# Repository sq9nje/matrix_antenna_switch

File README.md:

# 6x2 Matrix Antenna Switch

A complete antenna switching system that allows connecting two transceivers to up to 6 antennas with intelligent control and protection.

## Overview

This project implements a 6x2 matrix antenna switch system consisting of two main modules:

- **Relay Module**: High-power RF switching matrix with electromechanical relays
- **Interface Module**: ESP32-based control system with RS485 communication

The system provides flexible antenna routing while preventing simultaneous connection of both transceivers to the same antenna, ensuring equipment protection and operational safety.

## Key Features

### RF Performance
- **Power Handling**: Up to 1.5kW (full amateur license power)
- **Frequency Range**: DC to 50+ MHz with good performance
- **Protection**: Gas discharge tubes on all antenna ports for lightning/ESD protection
- **Isolation**: Decent port-to-port isolation
  - Better than 75dB below 10MHz
  - Better than 65dB below 30MHz
  - Better than 50dB below 50MHz

### Control System
- **ESP32-based**: WiFi-enabled microcontroller with comprehensive firmware
- **Multiple Interfaces**: Web UI, REST API, WebSocket, and serial command control
- **Network Features**: mDNS discovery (`antenna.local`), OTA updates, WiFi management
- **Smart Features**: Antenna conflict prevention, single radio mode, persistent settings
- **RS485 Interface**: Reliable half-duplex communication with automatic direction detection
- **Expandability**: SAO (Simple Add-On) connector for future enhancements

### Design Features
- **Modular Architecture**: Separate relay and interface modules for flexibility
- **Three-Relay Configuration**: Prevents transceiver conflicts while maintaining isolation
- **Professional PCB Design**: Multi-layer boards with proper grounding and shielding
- **Easy Assembly**: Through-hole components for straightforward construction

## System Architecture

The complete system consists of:

1. **[Relay Module](relay_module/hardware/README.md)**:
   - 6 antenna sections, each with 3 relays
   - Allows connection to Radio 1, Radio 2, or 50Ω dummy load
   - Comprehensive protection circuitry

2. **[Interface Module](interface_module/hardware/README.md)**: Provides intelligent control and communication
   - ESP32 DevKit v1 for processing and connectivity
   - RS485 interface for remote control
   - Expansion connector for additional features

## Documentation

### Hardware Documentation
- **[Relay Module Hardware](relay_module/hardware/README.md)** - Complete RF switching matrix documentation
- **[Interface Module Hardware](interface_module/hardware/README.md)** - ESP32 control system hardware

### Firmware Documentation  
- **[Interface Module Firmware](interface_module/firmware/README.md)** - ESP32 firmware with web interface, REST API, and OTA updates

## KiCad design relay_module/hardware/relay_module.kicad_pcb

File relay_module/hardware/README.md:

# Relay Module Hardware

This directory contains all hardware design files for the 6x2 Matrix Antenna Switch relay module, designed in KiCad.

## Overview

The relay module is a part of a 6x2 matrix antenna switch. It consists of six identical sections, one for each antenna. Each section allows connecting an antenna to Radio 1, Radio 2, or a 50-ohm dummy load (2W capacity). The design uses a popular three-relay configuration that prevents simultaneous connection of both transceivers to the same antenna while ensuring satisfactory isolation.

The relays are suitable for switching signals from transmitters at full amateur radio license power (1.5kW). All antenna ports are protected with gas discharge tubes (GDTs) to help protect radio inputs from high voltages generated during nearby lightning strikes or electrostatic charge buildup in antennas. However, the switch should not be considered a complete lightning protection solution.

**📋 [View Schematic (PDF)](images/relay_module.pdf)**

**🔧 [Interactive BOM](https://htmlpreview.github.io/?https://github.com/sq9nje/matrix_antenna_switch/blob/master/relay_module/hardware/bom/ibom.html){:target="_blank"}**

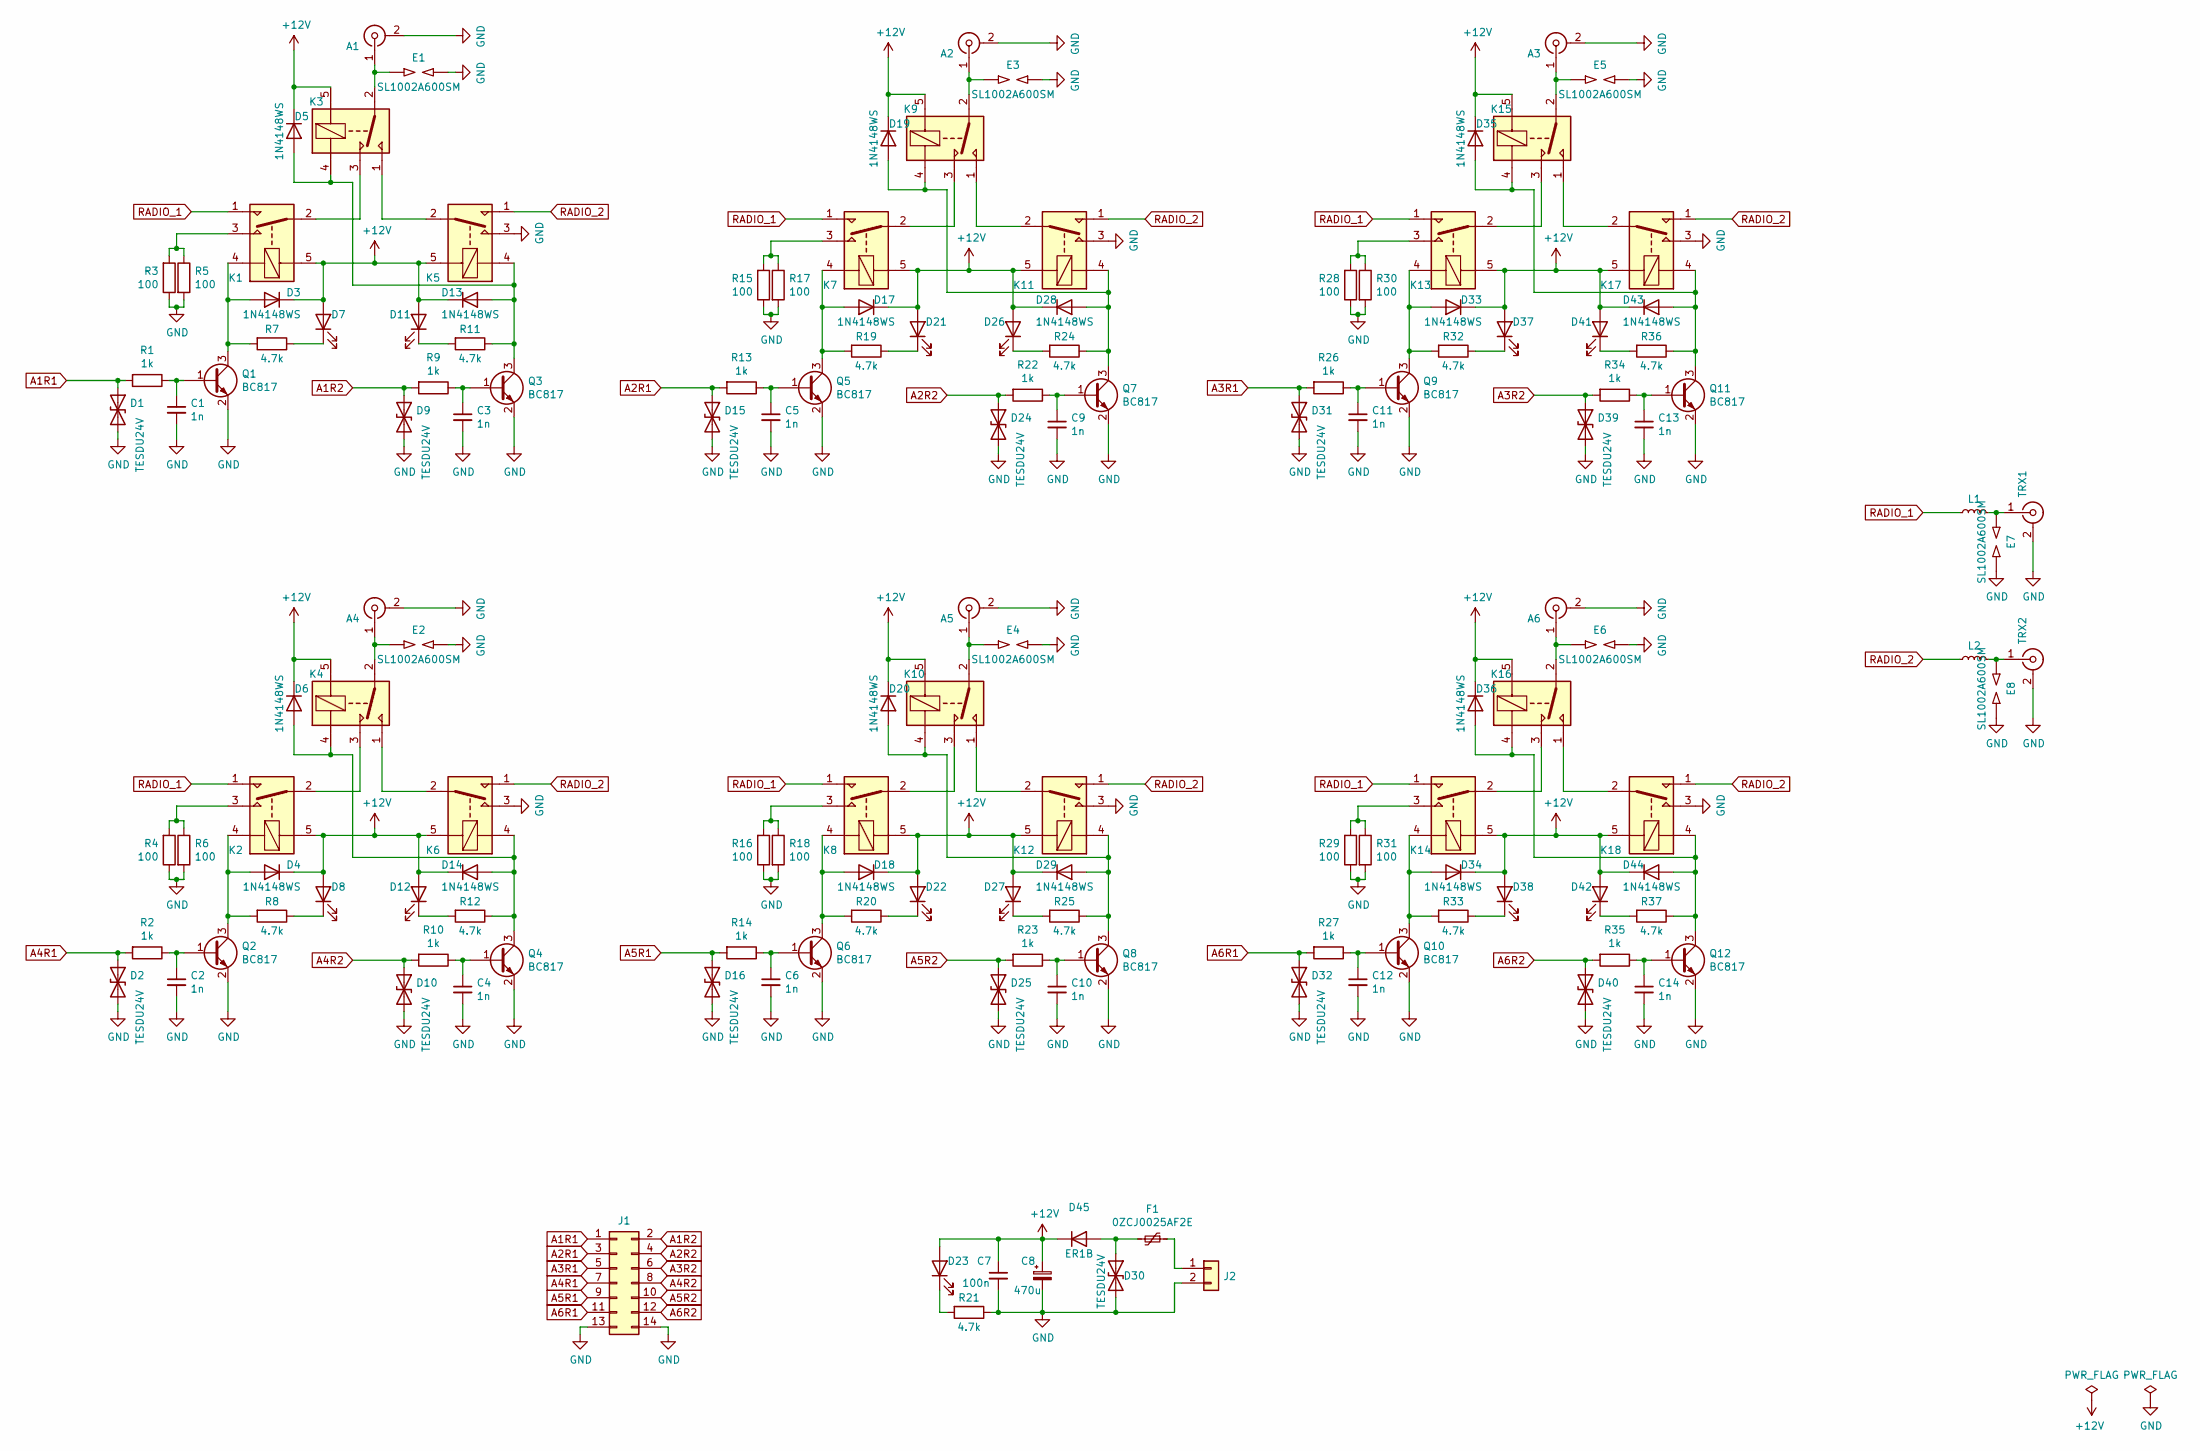
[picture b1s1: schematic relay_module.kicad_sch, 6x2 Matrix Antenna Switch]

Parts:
A1, A2, A3, A4, A5, A6: Conn_Coaxial; UC1-Square-2HolesRight
C1, C2, C3, C4, C5, C6, C9, C10, C11, C12, C13, C14: 1n; C_0805_2012Metric_Pad1.15x1.40mm_HandSolder
C7: 100n; C_0805_2012Metric_Pad1.15x1.40mm_HandSolder
C8: 470u; CP_Radial_D8.0mm_P3.50mm
D1, D2, D9, D10, D15, D16, D24, D25, D30, D31, D32, D39, D40: TESDU24V; R_0603_1608Metric_Pad1.05x0.95mm_HandSolder
D3, D4, D5, D6, D13, D14, D17, D18, D19, D20, D28, D29, D33, D34, D35, D36, D43, D44: 1N4148WS; D_SOD-323
D7, D8, D11, D12, D21, D22, D23, D26, D27, D37, D38, D41, D42: LED; LED_0805_2012Metric_Pad1.15x1.40mm_HandSolder
D45: ER1B; D_SMA_Handsoldering
E1, E2, E3, E4, E5, E6, E7, E8: SL1002A600SM; GDT_SL1002A_HandSolder
F1: 0ZCJ0025AF2E; Fuse_1206_3216Metric_Pad1.42x1.75mm_HandSolder
J1: Conn_02x07_Odd_Even; IDC-Header_2x07_P2.54mm_Vertical
J2: Conn_01x02; TerminalBlock_bornier-2_P5.08mm
K1, K2, K3, K4, K5, K6, K7, K8, K9, K10, K11, K12, K13, K14, K15, K16, K17, K18: Fujitsu_FTR-K1C; Relay_DPDT_Fujitsu_FTR-K1C
L1, L2: L_Small; R_Axial_DIN0411_L9.9mm_D3.6mm_P12.70mm_Horizontal
Q1, Q2, Q3, Q4, Q5, Q6, Q7, Q8, Q9, Q10, Q11, Q12: BC817; SOT-23
R1, R2, R9, R10, R13, R14, R22, R23, R26, R27, R34, R35: 1k; R_0805_2012Metric_Pad1.15x1.40mm_HandSolder
R3, R4, R5, R6, R15, R16, R17, R18, R28, R29, R30, R31: 100; R_2512_6332Metric_Pad1.52x3.35mm_HandSolder
R7, R8, R11, R12, R19, R20, R21, R24, R25, R32, R33, R36, R37: 4.7k; R_0805_2012Metric_Pad1.15x1.40mm_HandSolder
TRX1, TRX2: Conn_Coaxial; UC1-Square-2HolesRight

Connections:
+12V: C7.1, C8.1, D3.1 (K), D4.1 (K), D5.1 (K), D6.1 (K), D7.2 (A), D8.2 (A), D11.2 (A), D12.2 (A), D13.1 (K), D14.1 (K), D17.1 (K), D18.1 (K), D19.1 (K), D20.1 (K), D21.2 (A), D22.2 (A), D23.2 (A), D26.2 (A), D27.2 (A), D28.1 (K), D29.1 (K), D33.1 (K), D34.1 (K), D35.1 (K), D36.1 (K), D37.2 (A), D38.2 (A), D41.2 (A), D42.2 (A), D43.1 (K), D44.1 (K), D45.1 (K), K1.5, K2.5, K3.5, K4.5, K5.5, K6.5, K7.5, K8.5, K9.5, K10.5, K11.5, K12.5, K13.5, K14.5, K15.5, K16.5, K17.5, K18.5
A1R1: D1.1 (A1), J1.1, R1.2
A1R2: D9.1 (A1), J1.2, R9.2
A2R1: D15.1 (A1), J1.3, R13.2
A2R2: D24.1 (A1), J1.4, R22.2
A3R1: D31.1 (A1), J1.5, R26.2
A3R2: D39.1 (A1), J1.6, R34.2
A4R1: D2.1 (A1), J1.7, R2.2
A4R2: D10.1 (A1), J1.8, R10.2
A5R1: D16.1 (A1), J1.9, R14.2
A5R2: D25.1 (A1), J1.10, R23.2
A6R1: D32.1 (A1), J1.11, R27.2
A6R2: D40.1 (A1), J1.12, R35.2
GND: A1.2 (Ext), A2.2 (Ext), A3.2 (Ext), A4.2 (Ext), A5.2 (Ext), A6.2 (Ext), C1.2, C2.2, C3.2, C4.2, C5.2, C6.2, C7.2, C8.2, C9.2, C10.2, C11.2, C12.2, C13.2, C14.2, D1.2 (A2), D2.2 (A2), D9.2 (A2), D10.2 (A2), D15.2 (A2), D16.2 (A2), D24.2 (A2), D25.2 (A2), D30.2 (A2), D31.2 (A2), D32.2 (A2), D39.2 (A2), D40.2 (A2), E1.2, E2.2, E3.2, E4.2, E5.2, E6.2, E7.2, E8.2, J1.13, J1.14, J2.2, K5.3, K6.3, K11.3, K12.3, K17.3, K18.3, Q1.2 (E), Q2.2 (E), Q3.2 (E), Q4.2 (E), Q5.2 (E), Q6.2 (E), Q7.2 (E), Q8.2 (E), Q9.2 (E), Q10.2 (E), Q11.2 (E), Q12.2 (E), R3.1, R4.1, R5.2, R6.2, R15.1, R16.1, R17.2, R18.2, R21.1, R28.1, R29.1, R30.2, R31.2, TRX1.2 (Ext), TRX2.2 (Ext)
unnamed: A1.1 (In), E1.1, K3.2
unnamed: A2.1 (In), E3.1, K9.2
unnamed: A3.1 (In), E5.1, K15.2
unnamed: A4.1 (In), E2.1, K4.2
unnamed: A5.1 (In), E4.1, K10.2
unnamed: A6.1 (In), E6.1, K16.2
unnamed: C1.1, Q1.1 (B), R1.1
unnamed: C2.1, Q2.1 (B), R2.1
unnamed: C3.1, Q3.1 (B), R9.1
unnamed: C4.1, Q4.1 (B), R10.1
unnamed: C5.1, Q5.1 (B), R13.1
unnamed: C6.1, Q6.1 (B), R14.1
unnamed: C9.1, Q7.1 (B), R22.1
unnamed: C10.1, Q8.1 (B), R23.1
unnamed: C11.1, Q9.1 (B), R26.1
unnamed: C12.1, Q10.1 (B), R27.1
unnamed: C13.1, Q11.1 (B), R34.1
unnamed: C14.1, Q12.1 (B), R35.1
unnamed: D3.2 (A), K1.4, Q1.3 (C), R7.2
unnamed: D4.2 (A), K2.4, Q2.3 (C), R8.2
unnamed: D7.1 (K), R7.1
unnamed: D8.1 (K), R8.1
unnamed: D11.1 (K), R11.2
unnamed: D12.1 (K), R12.2
unnamed: D5.2 (A), D13.2 (A), K3.4, K5.4, Q3.3 (C), R11.1
unnamed: D6.2 (A), D14.2 (A), K4.4, K6.4, Q4.3 (C), R12.1
unnamed: D17.2 (A), K7.4, Q5.3 (C), R19.2
unnamed: D18.2 (A), K8.4, Q6.3 (C), R20.2
unnamed: D19.2 (A), D28.2 (A), K9.4, K11.4, Q7.3 (C), R24.1
unnamed: D20.2 (A), D29.2 (A), K10.4, K12.4, Q8.3 (C), R25.1
unnamed: D21.1 (K), R19.1
unnamed: D22.1 (K), R20.1
unnamed: D23.1 (K), R21.2
unnamed: D26.1 (K), R24.2
unnamed: D27.1 (K), R25.2
unnamed: D30.1 (A1), D45.2 (A), F1.2
unnamed: D33.2 (A), K13.4, Q9.3 (C), R32.2
unnamed: D34.2 (A), K14.4, Q10.3 (C), R33.2
unnamed: D35.2 (A), D43.2 (A), K15.4, K17.4, Q11.3 (C), R36.1
unnamed: D36.2 (A), D44.2 (A), K16.4, K18.4, Q12.3 (C), R37.1
unnamed: D37.1 (K), R32.1
unnamed: D38.1 (K), R33.1
unnamed: D41.1 (K), R36.2
unnamed: D42.1 (K), R37.2
unnamed: E7.1, L1.2, TRX1.1 (In)
unnamed: E8.1, L2.2, TRX2.1 (In)
unnamed: F1.1, J2.1
unnamed: K1.2, K3.3
unnamed: K1.3, R3.2, R5.1
unnamed: K2.2, K4.3
unnamed: K2.3, R4.2, R6.1
unnamed: K3.1, K5.2
unnamed: K4.1, K6.2
unnamed: K7.2, K9.3
unnamed: K7.3, R15.2, R17.1
unnamed: K8.3, R16.2, R18.1
unnamed: K10.1, K12.2
unnamed: K8.2, K10.3
unnamed: K9.1, K11.2
unnamed: K13.2, K15.3
unnamed: K13.3, R28.2, R30.1
unnamed: K14.2, K16.3
unnamed: K14.3, R29.2, R31.1
unnamed: K15.1, K17.2
unnamed: K16.1, K18.2
RADIO_1: K1.1, K2.1, K7.1, K8.1, K13.1, K14.1, L1.1
RADIO_2: K5.1, K6.1, K11.1, K12.1, K17.1, K18.1, L2.1

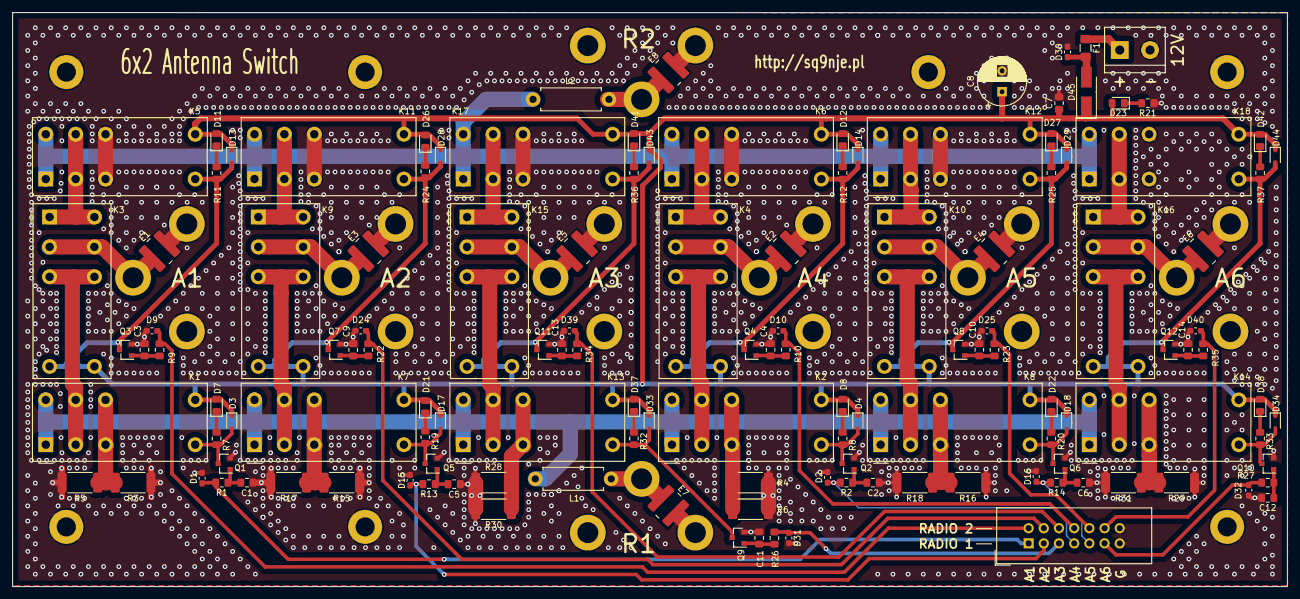
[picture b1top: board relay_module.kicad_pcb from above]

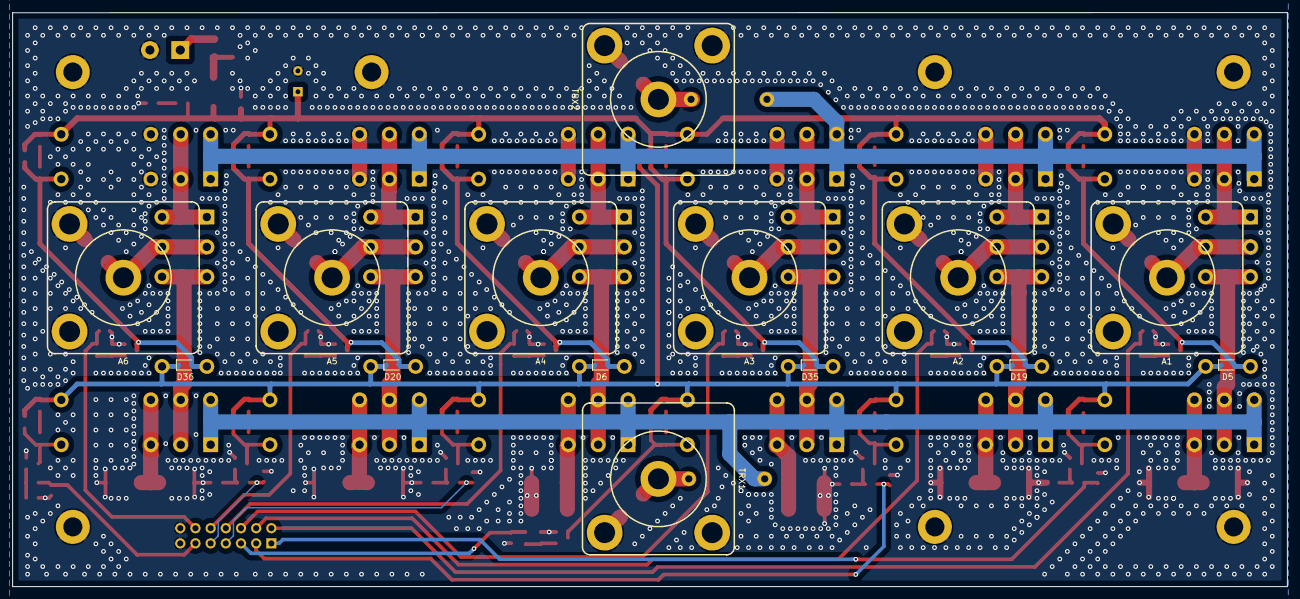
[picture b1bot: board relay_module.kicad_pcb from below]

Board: 2 copper layers, 213.3 x 96.0 mm, 147 parts (14 on the bottom side), 81 nets.

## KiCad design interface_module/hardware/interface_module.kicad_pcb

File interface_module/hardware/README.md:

# Interface Module Hardware

This directory contains all hardware design files for the 6x2 Matrix Antenna Switch Interface Module, designed in KiCad.

## Overview

The interface module is the control hub for the 6x2 matrix antenna switch system, designed by SQ9NJE (Quirky Solutions). The main component of the interface module is an ESP32 DevKit v1 development board. The module is also equipped with a half-duplex RS485 interface with automatic transmission direction detection and a 5V voltage regulator.

Next to the control signal connector for connecting the relay module, there is an additional SAO (Simple Add-On) connector. This connector provides access to I2C bus signals, two GPIO pins, and 3.3V power supply with ground. In the future, it may be used to extend the hardware capabilities of the switch, such as adding a display, band decoder, etc.

**📋 [View Schematic (PDF)](interface_module.pdf)**

**🔧 [Interactive BOM](https://htmlpreview.github.io/?https://github.com/sq9nje/matrix_antenna_switch/blob/master/interface_module/hardware/bom/ibom.html){:target="_blank"}**

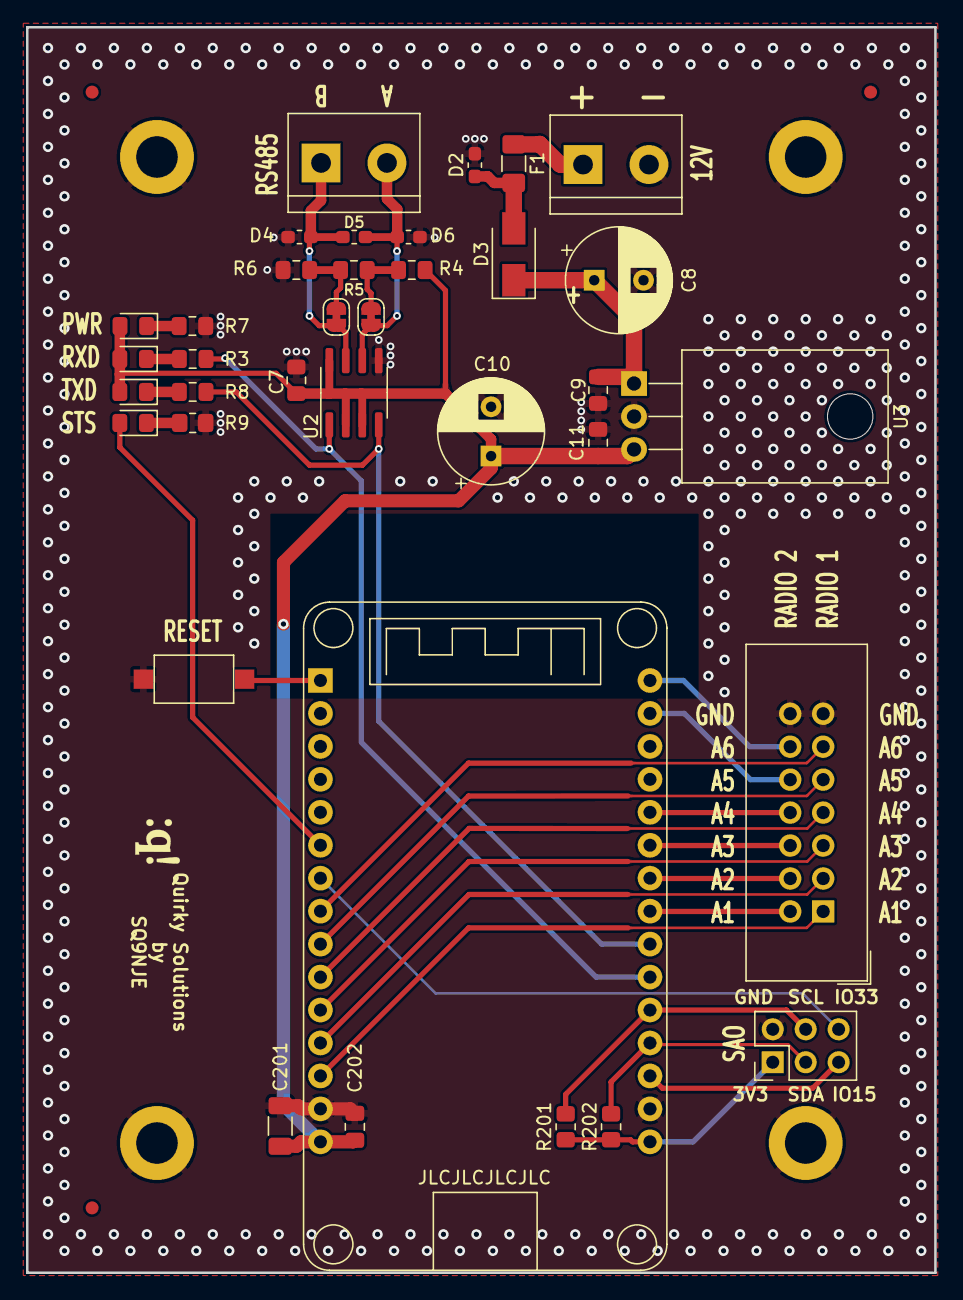
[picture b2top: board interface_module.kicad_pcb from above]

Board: 2 copper layers, 70.0 x 96.0 mm, 44 parts (0 on the bottom side), 34 nets.

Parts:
C7, C9, C11: 100n; C_0805_2012Metric_Pad1.15x1.40mm_HandSolder
C8, C10: 100u; CP_Radial_D8.0mm_P3.80mm
C201: 22u; C_1206_3216Metric_Pad1.33x1.80mm_HandSolder
C202: 100n; C_0805_2012Metric_Pad1.18x1.45mm_HandSolder
D2, D4, D5, D6: TSDU24V; R_0603_1608Metric_Pad1.05x0.95mm_HandSolder
D3: ER1B; D_SMA
D7, D8, D9, D10: LED_Small; LED_0805_2012Metric_Pad1.15x1.40mm_HandSolder
F1: 0ZCJ0025AF2E; Fuse_1206_3216Metric_Pad1.42x1.75mm_HandSolder
FID101, FID102, FID103: Fiducial; Fiducial_1mm_Mask2mm
H101, H102, H103, H104: MountingHole_Pad; MountingHole_3.2mm_M3_ISO7380_Pad
J2: Conn_02x07_Odd_Even; IDC-Header_2x07_P2.54mm_Vertical
J3, J4: Conn_01x02; TerminalBlock_bornier-2_P5.08mm
J201: Conn_02x03; PinHeader_2x03_P2.54mm_Vertical
JP1, JP2: Jumper_NC_Small; SolderJumper-2_P1.3mm_Bridged_RoundedPad1.0x1.5mm
R3, R7, R8: 2.2k; R_0805_2012Metric_Pad1.15x1.40mm_HandSolder
R4, R6: 1k; R_0805_2012Metric_Pad1.15x1.40mm_HandSolder
R5: 120; R_0805_2012Metric_Pad1.15x1.40mm_HandSolder
R9: 470; R_0805_2012Metric_Pad1.20x1.40mm_HandSolder
R201, R202: 10k; R_0805_2012Metric_Pad1.20x1.40mm_HandSolder
Ref**: Val**; qs_logo
SW1: SW_Push; SW_SPST_CK_RS282G05A3
U2: MAX13487; SOIC-8_3.9x4.9mm_P1.27mm
U3: LM7805_TO220; TO-220-3_Horizontal_TabDown
U201: esp32_devkit_v1_doit

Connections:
+3V3: J201.1 (+12V), R201.1, R202.1, U201.16 (3.3v)
+5V: C7.2, C10.1, C11.1, C201.1, C202.1, D7.2 (A), D8.2 (A), D9.2 (A), R4.1, U2.2 (~RE), U2.3 (~SHDN), U2.8 (VCC), U3.3 (VO), U201.15 (VIN)
/ESP32/GPIO15: J201.5 (GND), U201.18 (GPIO15)
/ESP32/GPIO33: J201.6 (GND), U201.7 (GPIO33)
/ESP32/SCL: J201.4 (GND), R201.2, U201.20 (GPIO4)
/ESP32/SDA: J201.3 (GND), R202.2, U201.19 (GPIO2)
A1R1: J2.1, U201.13 (GPIO13)
A1R2: J2.2, U201.23 (GPIO5)
A2R1: J2.3, U201.12 (GPIO12)
A2R2: J2.4, U201.24 (GPIO18)
A3R1: J2.5, U201.11 (GPIO14)
A3R2: J2.6, U201.25 (GPIO19)
A4R1: J2.7, U201.10 (GPIO27)
A4R2: J2.8, U201.26 (GPIO21)
A5R1: J2.9, U201.9 (GPIO26)
A5R2: J2.10, U201.29 (GPIO22)
A6R1: J2.11, U201.8 (GPIO25)
A6R2: J2.12, U201.30 (GPIO23)
GND: C7.1, C8.2, C9.2, C10.2, C11.2, C201.2, C202.2, D2.2 (A2), D4.1 (A1), D6.2 (A2), H101.1, H102.1, H103.1, H104.1, J2.13, J2.14, J3.2, J201.2 (+12V), R6.2, R7.2, R9.2, SW1.1, U2.5 (GND), U3.2 (GND), U201.14 (GND), U201.17 (GND)
unnamed: D2.1 (A1), D3.2 (A), F1.2
unnamed: C8.1, C9.1, D3.1 (K), U3.1 (VI)
unnamed: D7.1 (K), R3.1
unnamed: D8.1 (K), R7.1
unnamed: D9.1 (K), R8.1
unnamed: D10.2 (A), U201.6 (GPIO32)
unnamed: D10.1 (K), R9.1
unnamed: F1.1, J3.1
unnamed: JP1.2, R4.2, R5.1
unnamed: JP2.2, R5.2, R6.1
unnamed: SW1.2, U201.1 (EN)
RS485_A: D5.2 (A2), D6.1 (A1), J4.2, JP1.1, U2.6 (A)
RS485_B: D4.2 (A2), D5.1 (A1), J4.1, JP2.1, U2.7 (B)
RXD2: R3.2, U2.1 (RO), U201.21 (GPIO16)
TXD2: R8.2, U2.4 (DI), U201.22 (GPIO17)

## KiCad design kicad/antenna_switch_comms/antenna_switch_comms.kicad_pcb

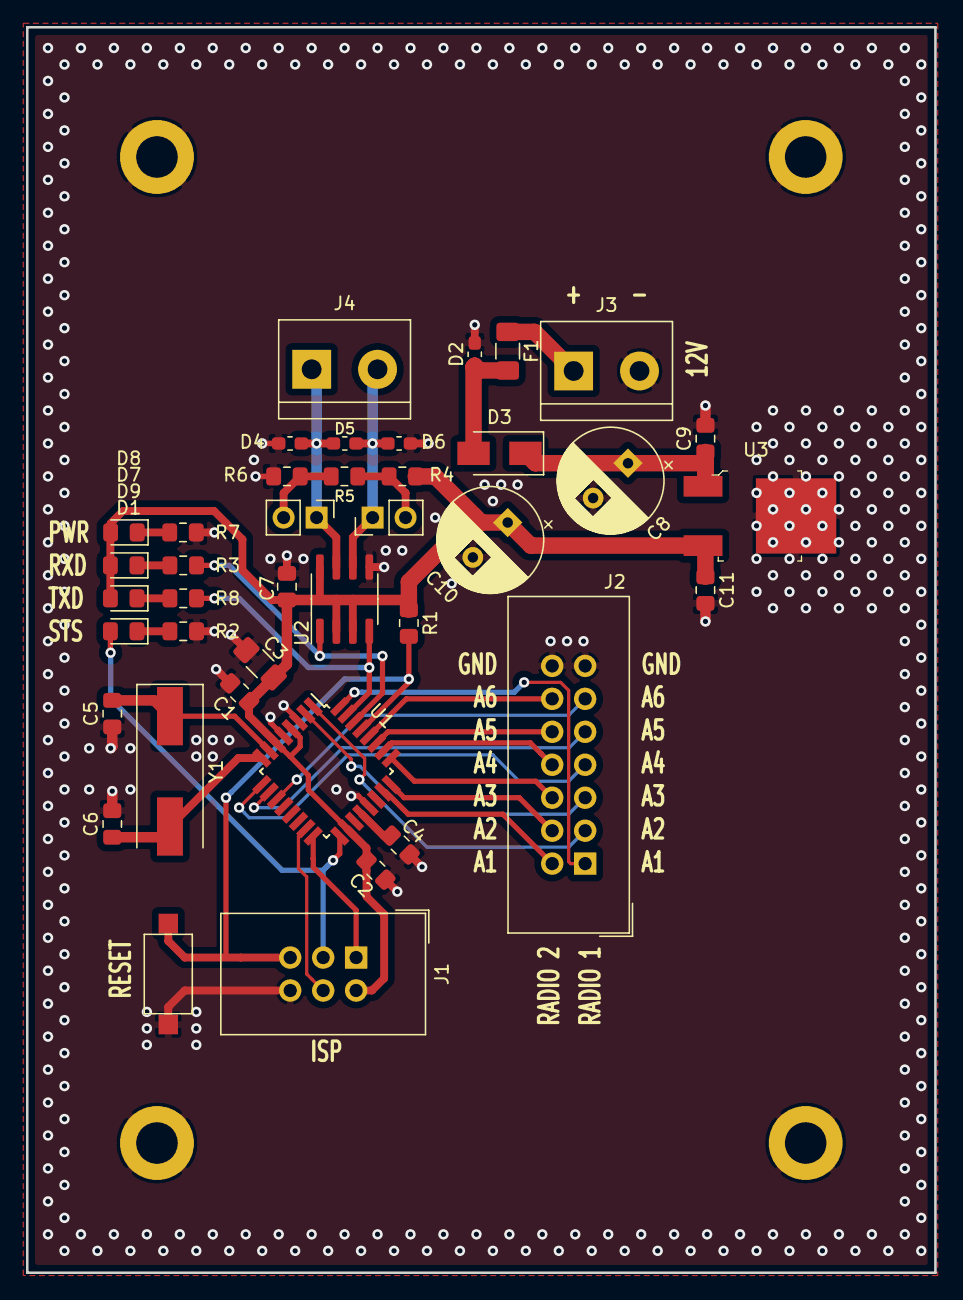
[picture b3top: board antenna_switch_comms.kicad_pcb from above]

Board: 2 copper layers, 70.0 x 96.0 mm, 40 parts (0 on the bottom side), 34 nets.

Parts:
C1, C2, C4, C7, C9, C11: 100n; C_0805_2012Metric_Pad1.15x1.40mm_HandSolder
C3: 4.7u; C_1206_3216Metric_Pad1.42x1.75mm_HandSolder
C5, C6: 18p; C_0805_2012Metric_Pad1.15x1.40mm_HandSolder
C8, C10: 100u; CP_Radial_D8.0mm_P3.80mm
D1, D7, D8, D9: LED_Small; LED_0805_2012Metric_Pad1.15x1.40mm_HandSolder
D2, D4, D5, D6: TESDU24V; R_0603_1608Metric_Pad1.05x0.95mm_HandSolder
D3: ER1B; D_SMA
F1: 0ZCJ0025AF2E; Fuse_1206_3216Metric_Pad1.42x1.75mm_HandSolder
J1: AVR-ISP-6; IDC-Header_2x03_P2.54mm_Vertical
J2: Conn_02x07_Odd_Even; IDC-Header_2x07_P2.54mm_Vertical
J3, J4: Conn_01x02; TerminalBlock_bornier-2_P5.08mm
JP1, JP2: Jumper_NC_Small; PinHeader_1x02_P2.54mm_Vertical
R1, R4, R6: 1k; R_0805_2012Metric_Pad1.15x1.40mm_HandSolder
R2, R3, R7, R8: 2.2k; R_0805_2012Metric_Pad1.15x1.40mm_HandSolder
R5: 120; R_0805_2012Metric_Pad1.15x1.40mm_HandSolder
SW1: SW_Push; SW_SPST_CK_RS282G05A3
U1: ATmega328P-AU; TQFP-32_7x7mm_P0.8mm
U2: MAX13487; SOIC-8_3.9x4.9mm_P1.27mm
U3: MC7805BDTRKG; TO-252-3
Y1: 16M; Crystal_SMD_HC49-SD

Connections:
+5V: C1.1, C2.1, C3.1, C7.2, C10.1, C11.1, D7.2, D8.2, D9.2, J1.2, R1.1, R4.1, U1.4, U1.6, U1.18, U2.2, U2.3, U2.8, U3.3
A1R1: J2.1, U1.32
A1R2: J2.2, U1.23
A2R1: J2.3, U1.1
A2R2: J2.4, U1.24
A3R1: J2.5, U1.2
A3R2: J2.6, U1.25
A4R1: J2.7, U1.9
A4R2: J2.8, U1.26
A5R1: J2.9, U1.10
A5R2: J2.10, U1.27
A6R1: J2.11, U1.11
A6R2: J2.12, U1.28
GND: C1.2, C2.2, C3.2, C4.1, C5.1, C6.1, C7.1, C8.2, C9.2, C10.2, C11.2, D2.2, D4.1, D6.2, J1.6, J2.13, J2.14, J3.2, R2.2, R6.2, R7.2, SW1.1, U1.3, U1.5, U1.21, U2.5, U3.4
MISO: J1.1, U1.16
MOSI: J1.4, U1.15
unnamed: C4.2, U1.20
unnamed: C5.2, U1.7, Y1.1
unnamed: C6.2, U1.8, Y1.2
unnamed: C8.1, C9.1, D3.1, U3.1
unnamed: D1.1, R2.1
unnamed: D2.1, D3.2, F1.2
unnamed: D7.1, R3.1
unnamed: D8.1, R7.1
unnamed: D9.1, R8.1
unnamed: F1.1, J3.1
unnamed: JP1.2, R4.2, R5.1
unnamed: JP2.2, R5.2, R6.1
RESET: J1.5, R1.2, SW1.2, U1.29
RS485_A: D5.2, D6.1, J4.2, JP1.1, U2.6
RS485_B: D4.2, D5.1, J4.1, JP2.1, U2.7
RXD: R3.2, U1.30, U2.1
SCK: D1.2, J1.3, U1.17
TXD: R8.2, U1.31, U2.4

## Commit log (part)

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2019-09-29 Initial schematic
2019-09-29 Schematic libs
2019-09-29 Add cache lib for cadlab.io
2019-09-29 Backlink to CADLAB.io has been added.
2019-09-29 Compensation coils
2020-05-09 Relays in series to increase isolation
2020-05-10 Add datasheets
2020-05-10 Initial PCB layout work
2020-05-10 Some more layout
2020-05-11 Some layout and routing
2020-05-13 routing finished
2020-05-13 top silk
2020-05-14 top ground plane
2020-05-14 bottom silk
2020-05-14 vias, lots of vias
2020-05-16 reverse protection diode
2020-05-16 less vias
2020-05-19 Comms module
2020-05-27 firmware
2020-05-29 FW modifications
2020-07-10 Desktop app - initial
2021-03-20 Bump jinja2 from 2.11.2 to 2.11.3 in /app
    Bumps [jinja2](https://github.com/pallets/jinja) from 2.11.2 to 2.11.3.
    - [Release notes](https://github.com/pallets/jinja/releases)
    - [Changelog](https://github.com/pallets/jinja/blob/master/CHANGES.rst)
    - [Commits](https://github.com/pallets/jinja/compare/2.11.2...2.11.3)
2021-05-08 Bump eventlet from 0.25.2 to 0.31.0 in /app
    Bumps [eventlet](https://github.com/eventlet/eventlet) from 0.25.2 to 0.31.0.
    - [Release notes](https://github.com/eventlet/eventlet/releases)
    - [Changelog](https://github.com/eventlet/eventlet/blob/master/NEWS)
    - [Commits](https://github.com/eventlet/eventlet/compare/v0.25.2...v0.31.0)
2022-08-14 test
2023-10-23 Add drilling template
2023-10-23 KiCAD project
2025-06-04 ESP32 Coms module HW
2025-07-08 ESP32 firmware with bad pinout hack
2025-07-08 mDNS support
2025-07-08 Status page, reset, reboot
2025-07-08 Fix hostname bug
2025-07-08 Refactor
2025-07-26 ESP32 Interface Module HW
2025-07-26 ESP32 Interface Module (#3)
2025-07-26 Rearrange files
2025-09-09 Enclosure top
2025-09-09 OTA updates
2025-09-09 Interface module FW Documentation
2025-09-09 Relay Module documentation
2025-09-09 Interface Module documentation
2025-09-09 Docs
2025-10-07 Bump python-socketio in /archive/rs485_interface_module/app
    Bumps [python-socketio](https://github.com/miguelgrinberg/python-socketio) from 4.6.0 to 5.14.0.
    - [Release notes](https://github.com/miguelgrinberg/python-socketio/releases)
    - [Changelog](https://github.com/miguelgrinberg/python-socketio/blob/main/CHANGES.md)
    - [Commits](https://github.com/miguelgrinberg/python-socketio/compare/v4.6.0...v5.14.0)
    ---
    updated-dependencies:
2025-10-28 Initial GHA workflow test
2025-10-28 Initial GHA workflow for building the firmware (#10)
2025-10-28 Bump jinja2 from 2.11.2 to 3.1.6 in /archive/rs485_interface_module/app
    Bumps [jinja2](https://github.com/pallets/jinja) from 2.11.2 to 3.1.6.
    - [Release notes](https://github.com/pallets/jinja/releases)
    - [Changelog](https://github.com/pallets/jinja/blob/main/CHANGES.rst)
    - [Commits](https://github.com/pallets/jinja/compare/2.11.2...3.1.6)
    ---
    updated-dependencies:
2025-10-28 Bump werkzeug from 1.0.1 to 3.0.6 in /archive/rs485_interface_module/app
    Bumps [werkzeug](https://github.com/pallets/werkzeug) from 1.0.1 to 3.0.6.
    - [Release notes](https://github.com/pallets/werkzeug/releases)
    - [Changelog](https://github.com/pallets/werkzeug/blob/main/CHANGES.rst)
    - [Commits](https://github.com/pallets/werkzeug/compare/1.0.1...3.0.6)
    ---
    updated-dependencies:
2025-10-28 Bump dnspython in /archive/rs485_interface_module/app
    Bumps [dnspython](https://github.com/rthalley/dnspython) from 1.16.0 to 2.6.1.
    - [Release notes](https://github.com/rthalley/dnspython/releases)
    - [Changelog](https://github.com/rthalley/dnspython/blob/main/doc/whatsnew.rst)
    - [Commits](https://github.com/rthalley/dnspython/compare/v1.16.0...v2.6.1)
    ---
    updated-dependencies:
2025-10-28 Bump eventlet in /archive/rs485_interface_module/app
    Bumps [eventlet](https://github.com/eventlet/eventlet) from 0.25.2 to 0.40.3.
    - [Changelog](https://github.com/eventlet/eventlet/blob/master/NEWS)
    - [Commits](https://github.com/eventlet/eventlet/compare/v0.25.2...0.40.3)
    ---
    updated-dependencies:
    - dependency-name: eventlet
2025-11-02 Release workflow
2025-11-02 GHA - release firmware (#15)
2025-11-02 Fix release workflow
2026-03-22 Fix relay pin assignment
2026-03-22 Fix relay pin assignment (#16)
2026-03-22 Display only antennas with a description
2026-03-22 Display only antennas with a description (#17)
2026-03-22 Fix disabled button in swapping mode
2026-03-22 Fix disabled button in swapping mode (#19)
2026-03-22 New UI styles
2026-03-22 New UI styles (#20)
2026-03-22 initial band badges
2026-03-22 rainbow badges
2026-03-22 settings layout
2026-03-22 natenna config struct refactor
2026-03-22 Band labels (#21)
2026-03-22 Initial OTRSP support
2026-03-22 Initial OTRSP support (#22)
